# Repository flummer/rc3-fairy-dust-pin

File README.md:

# Fairy Dust mini PCB pin for RC3

This is a small PCB pin badge, heavily inspired by the [RC3 styleguide](https://styleguide.rc3.world/RC3%20Style%20Guide%20Essentials.pdf). It's designed to be small, easy to assemble and hopefully many will manage to get some before the event, and be able to share a little bit of physical #badgelife, in this time of virtual events.

## Making your own

If you want to make your own, I have included the gerbers, in case you don't want to install the nightly version of KiCad.

There is also a [shared projects at OSHPark](https://oshpark.com/shared_projects/DYZInoHY), and this is designed for the standard purple PCBs. It's designed to be exactly 2 square inches, so for USD 10 you get 3 pcs. shipped anywhere, though the standard shipping might take a bit to arrive.

The parts needed for this pin is simply 4 white 0603 LEDs, a series resistor, also 0603, to limit the current a bit (I'll try with a 1K to begin with), a CR1220 coin cell holder (I'm planning on using a [Q&J CR1220-2 from LCSC](https://lcsc.com/product-detail/Battery-Holders-Clips-Contacts_Q-J-CR1220-2_C70381.html)) and then a little round brooch clasp/tie tack pin (I got some on ebay, but a DIY/craft supply store might also have them).

## Please share

If you decide to make this badge or a variant of it, please share images so we can all see it and get inspired. If sharing on social media, please use the #badgelife tag and please let [me](https://thomasflummer.com/) know, I would love to see what you have made!

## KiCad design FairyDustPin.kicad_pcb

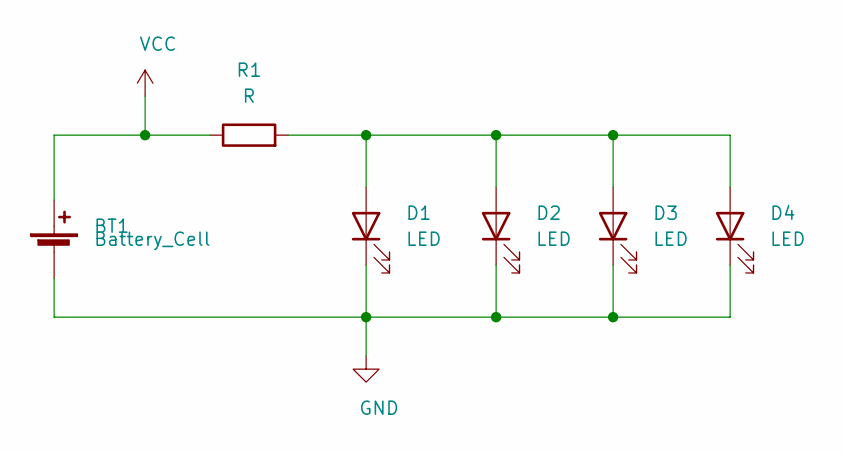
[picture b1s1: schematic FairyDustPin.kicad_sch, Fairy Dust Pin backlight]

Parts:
BT1: Battery_Cell; CR1220-2
D1, D2, D3, D4: LED; LED_0603_1608Metric_Pad1.05x0.95mm_HandSolder
R1: R; R_0603_1608Metric_Pad0.98x0.95mm_HandSolder

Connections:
GND: BT1.2 (-), D1.1 (K), D2.1 (K), D3.1 (K), D4.1 (K)
unnamed: D1.2 (A), D2.2 (A), D3.2 (A), D4.2 (A), R1.2
VCC: BT1.1 (+), R1.1

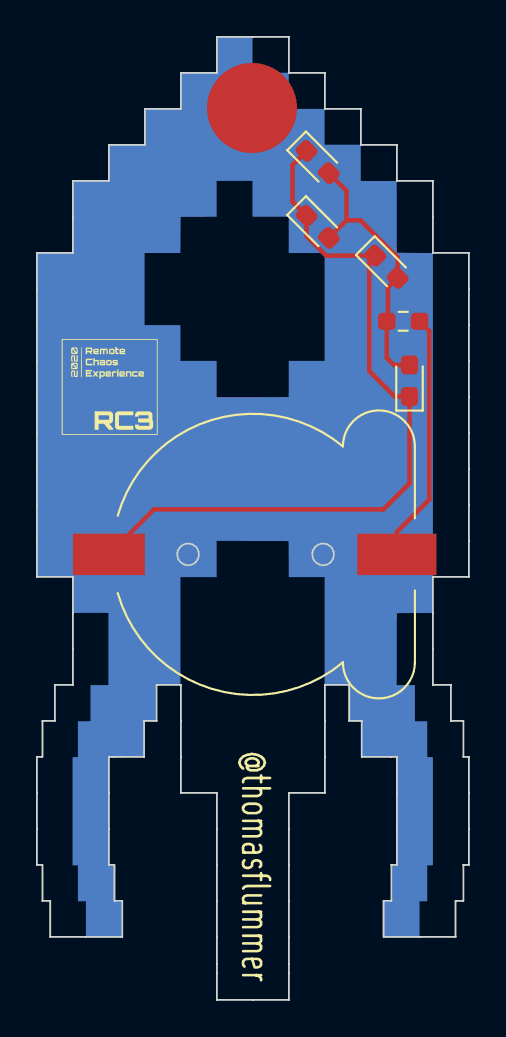
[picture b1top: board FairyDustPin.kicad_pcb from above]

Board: 2 copper layers, 24.0 x 53.5 mm, 6 parts (0 on the bottom side), 3 nets.
